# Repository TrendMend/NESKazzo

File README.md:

# NESKazzo
Welcome! This repository is deticated to replicating and working on the Kazzo in Eagle CAD to reference, and work off of.
# How to use this repository
First you have to clone it to your local drive, then add all the libraries in the folder with the same name to your Eagle installation, then tell Eagle to use them by right clicking libraries in your control panel and selecting "Use All". Afterwards, you need to move the NES folder inside projects, into your projects folder, then you need to select "Use All" in the same way you did it for the libraries. Once it changes to active, it will be indicated via a green light.
## What needs to be done?
1. Test on breadboard.
2. Work on BRD file.
3. Add OSHPark page and test.
4. Work on the firmware.
### Why haven't you done any of this yet?
Because I am lazy and stupid :P
### Important pages
NESDEV fourm post: https://forums.nesdev.com/viewtopic.php?f=9&t=7912&start=60 <br>
OSDN project page: https://osdn.net/projects/unagi/wiki/kazzo_intro_en

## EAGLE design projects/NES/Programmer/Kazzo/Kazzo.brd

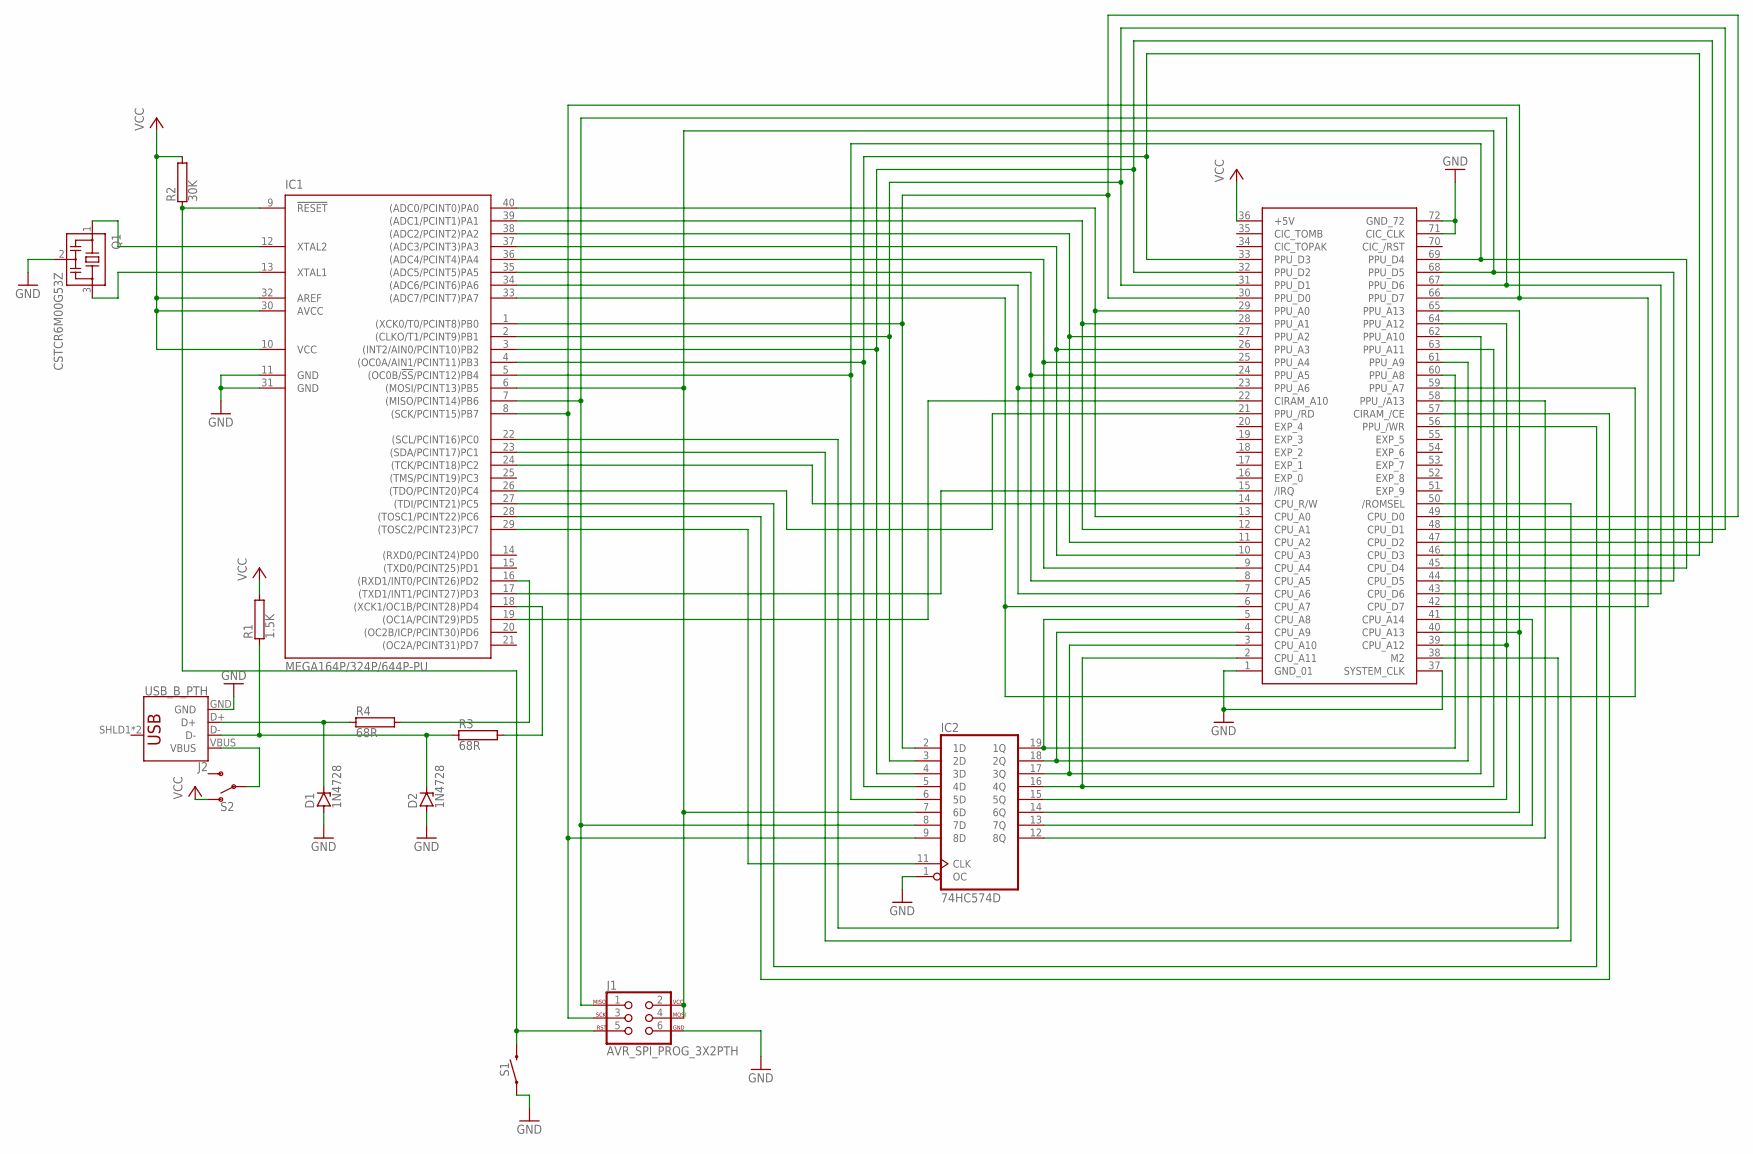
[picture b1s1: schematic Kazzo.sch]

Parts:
D1, D2: 1N4728; DO41Z10
IC1: MEGA164P/324P/644P-PU; DIL40
IC2: 74HC574D; SO20W
IC3: NES_CONNECTOR
J1: AVR_SPI_PROG_3X2PTH; 2X3
J2: USB_B_PTH; USB-B-PTH
Q1: CSTCR6M00G53Z; CSTCR6M
R1: 1.5K; AC01
R2: 30K; AC01
R3, R4: 68R; AC01
S1: MOMENTARY-SWITCH-SPST-PTH-6.0MM-KIT; TACTILE_SWITCH_PTH_6.0MM_KIT
S2: SWITCH-SPDT-PTH-11.6X4.0MM; SWITCH_SPDT_PTH_11.6X4.0MM

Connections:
GND: D1.A, D2.A, IC1.11 (GND), IC1.31 (GND), IC2.1 (OC), IC2.10 (GND), IC3.1 (GND_01), IC3.37 (SYSTEM_CLK), IC3.71 (CIC_CLK), IC3.72 (GND_72), J1.6, J2.GND, Q1.2, S1.1
unnamed: IC1.40 ((ADC0/PCINT0)PA0), IC3.13 (CPU_A0), IC3.29 (PPU_A0)
unnamed: IC1.39 ((ADC1/PCINT1)PA1), IC3.12 (CPU_A1), IC3.28 (PPU_A1)
unnamed: IC1.38 ((ADC2/PCINT2)PA2), IC3.11 (CPU_A2), IC3.27 (PPU_A2)
unnamed: IC1.37 ((ADC3/PCINT3)PA3), IC3.10 (CPU_A3), IC3.26 (PPU_A3)
unnamed: IC1.36 ((ADC4/PCINT4)PA4), IC3.9 (CPU_A4), IC3.25 (PPU_A4)
unnamed: IC1.35 ((ADC5/PCINT5)PA5), IC3.8 (CPU_A5), IC3.24 (PPU_A5)
unnamed: IC1.34 ((ADC6/PCINT6)PA6), IC3.7 (CPU_A6), IC3.23 (PPU_A6)
unnamed: IC1.33 ((ADC7/PCINT7)PA7), IC3.6 (CPU_A7), IC3.59 (PPU_A7)
unnamed: IC2.19 (1Q), IC3.5 (CPU_A8), IC3.60 (PPU_A8)
unnamed: IC2.18 (2Q), IC3.4 (CPU_A9), IC3.61 (PPU_A9)
unnamed: IC2.17 (3Q), IC3.3 (CPU_A10), IC3.62 (PPU_A10)
unnamed: IC2.16 (4Q), IC3.2 (CPU_A11), IC3.63 (PPU_A11)
unnamed: IC2.15 (5Q), IC3.39 (CPU_A12), IC3.64 (PPU_A12)
unnamed: IC2.14 (6Q), IC3.40 (CPU_A13), IC3.65 (PPU_A13)
unnamed: IC2.13 (7Q), IC3.41 (CPU_A14)
unnamed: IC2.12 (8Q), IC3.58 (PPU_/A13)
unnamed: IC1.1 ((XCK0/T0/PCINT8)PB0), IC2.2 (1D), IC3.30 (PPU_D0), IC3.49 (CPU_D0)
unnamed: IC1.2 ((CLKO/T1/PCINT9)PB1), IC2.3 (2D), IC3.31 (PPU_D1), IC3.48 (CPU_D1)
unnamed: IC1.3 ((INT2/AIN0/PCINT10)PB2), IC2.4 (3D), IC3.32 (PPU_D2), IC3.47 (CPU_D2)
unnamed: IC1.4 ((OC0A/AIN1/PCINT11)PB3), IC2.5 (4D), IC3.33 (PPU_D3), IC3.46 (CPU_D3)
unnamed: IC1.5 ((OC0B/!SS!/PCINT12)PB4), IC2.6 (5D), IC3.45 (CPU_D4), IC3.69 (PPU_D4)
unnamed: IC1.22 ((SCL/PCINT16)PC0), IC3.38 (M2)
unnamed: IC1.23 ((SDA/PCINT17)PC1), IC3.50 (/ROMSEL)
unnamed: IC1.24 ((TCK/PCINT18)PC2), IC3.14 (CPU_R/W)
unnamed: IC1.26 ((TDO/PCINT20)PC4), IC3.21 (PPU_/RD)
unnamed: IC1.27 ((TDI/PCINT21)PC5), IC3.56 (PPU_/WR)
unnamed: IC1.28 ((TOSC1/PCINT22)PC6), IC3.57 (CIRAM_/CE)
unnamed: IC1.29 ((TOSC2/PCINT23)PC7), IC2.11 (CLK)
unnamed: IC1.16 ((RXD1/INT0/PCINT26)PD2), R4.2
unnamed: IC1.18 ((XCK1/OC1B/PCINT28)PD4), R3.2
unnamed: IC1.6 ((MOSI/PCINT13)PB5), IC2.7 (6D), IC3.44 (CPU_D5), IC3.68 (PPU_D5), J1.2, J1.4
unnamed: IC1.7 ((MISO/PCINT14)PB6), IC2.8 (7D), IC3.43 (CPU_D6), IC3.67 (PPU_D6), J1.1
unnamed: IC1.8 ((SCK/PCINT15)PB7), IC2.9 (8D), IC3.42 (CPU_D7), IC3.66 (PPU_D7), J1.3
unnamed: IC1.9 (!RESET), J1.5, R2.1, S1.3 (2)
unnamed: D1.C, J2.D+, R4.1
unnamed: D2.C, J2.D-, R1.1, R3.1
unnamed: J2.VBUS, S2.2
unnamed: IC1.17 ((TXD1/INT1/PCINT27)PD3), IC3.15 (/IRQ)
unnamed: IC1.12 (XTAL2), Q1.1
unnamed: IC1.13 (XTAL1), Q1.3
unnamed: IC1.19 ((OC1A/PCINT29)PD5), IC3.22 (CIRAM_A10)
VCC: IC1.10 (VCC), IC1.30 (AVCC), IC1.32 (AREF), IC2.20 (VCC), IC3.36 (+5V), R1.2, R2.2, S2.1 (O)

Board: 2 copper layers, 14 parts (0 on the bottom side), 43 nets, no tracks yet.

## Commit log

2019-09-01 Added Libraries
    Added required libraries for my Eagle CAD files.
2019-09-01 Added CAD Files
    Added Eagle CAD files, and fixed folder naming.
2019-09-01 Update README.md
    Added info on setting project up.
2019-09-01 Update README.md
    Added <br>

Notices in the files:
parts and their libraries:
SparkFun-Connectors: Licensing: Creative Commons ShareAlike 4.0 International - https://creativecommons.org/licenses/by-sa/4.0
